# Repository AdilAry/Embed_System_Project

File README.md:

Battery management system for a 4-cell LiFePO4 pack: plug-in board for an STM32 NUCLEO-L152RE with per-cell voltage, current and temperature measurement, MOSFET charge/discharge switching, and Modbus RTU over RS-485. Designed in KiCad, simulated in LTspice, built and tested.

---
### Project specification;
---
#### Battery details:
**4 cell Lithium Iron Phosphate battery.**

Cell voltage: 3.2 V

Cell capacity: 105 Ah

Charge voltage maximum: 3.65 V

Discharge cutoff voltage: 2.5 V

---
Battery full specifications can be found here: https://www.18650batterystore.com/products/eve-lf105

---
#### Requirements;
- Temperature monitoring (via two sensors).
- Individual battery cell voltages measurement.
- MOSFET driven switch (both charging and discharging).
- Current measurement, including over current protection (10A).
- STM32 controller with over/under voltage per cell (2.5V min, 3.65V max. per cell), over/under temperature (charge: 0C to 40C and discharge: -20C to 40C).
- Plugin design to connect a NUCLEO-L152RE board to the BMS circuit.

---
### Platform/software choices;
Version Control - Git, GitHub.

CAD - KiCAD.

Circuit Simulation - LTspice.

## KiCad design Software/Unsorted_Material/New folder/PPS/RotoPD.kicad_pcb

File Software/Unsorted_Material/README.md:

# helloooee

## Getting started

To make it easy for you to get started with GitLab, here's a list of recommended next steps.

Already a pro? Just edit this README.md and make it your own. Want to make it easy? [Use the template at the bottom](#editing-this-readme)!

## Add your files

- [ ] [Create](https://docs.gitlab.com/ee/user/project/repository/web_editor.html#create-a-file) or [upload](https://docs.gitlab.com/ee/user/project/repository/web_editor.html#upload-a-file) files
- [ ] [Add files using the command line](https://docs.gitlab.com/topics/git/add_files/#add-files-to-a-git-repository) or push an existing Git repository with the following command:

```
cd existing_repo
git remote add origin http://gitlab.local/root/hello.git
git branch -M main
git push -uf origin main
```

## Integrate with your tools

- [ ] [Set up project integrations](http://gitlab.local/root/hello/-/settings/integrations)

## Collaborate with your team

- [ ] [Invite team members and collaborators](https://docs.gitlab.com/ee/user/project/members/)
- [ ] [Create a new merge request](https://docs.gitlab.com/ee/user/project/merge_requests/creating_merge_requests.html)
- [ ] [Automatically close issues from merge requests](https://docs.gitlab.com/ee/user/project/issues/managing_issues.html#closing-issues-automatically)
- [ ] [Enable merge request approvals](https://docs.gitlab.com/ee/user/project/merge_requests/approvals/)
- [ ] [Set auto-merge](https://docs.gitlab.com/user/project/merge_requests/auto_merge/)

## Test and Deploy

Use the built-in continuous integration in GitLab.

- [ ] [Get started with GitLab CI/CD](https://docs.gitlab.com/ee/ci/quick_start/)
- [ ] [Analyze your code for known vulnerabilities with Static Application Security Testing (SAST)](https://docs.gitlab.com/ee/user/application_security/sast/)
- [ ] [Deploy to Kubernetes, Amazon EC2, or Amazon ECS using Auto Deploy](https://docs.gitlab.com/ee/topics/autodevops/requirements.html)
- [ ] [Use pull-based deployments for improved Kubernetes management](https://docs.gitlab.com/ee/user/clusters/agent/)
- [ ] [Set up protected environments](https://docs.gitlab.com/ee/ci/environments/protected_environments.html)

***

# Editing this README

When you're ready to make this README your own, just edit this file and use the handy template below (or feel free to structure it however you want - this is just a starting point!). Thanks to [makeareadme.com](https://www.makeareadme.com/) for this template.

## Suggestions for a good README

Every project is different, so consider which of these sections apply to yours. The sections used in the template are suggestions for most open source projects. Also keep in mind that while a README can be too long and detailed, too long is better than too short. If you think your README is too long, consider utilizing another form of documentation rather than cutting out information.

## Name
Choose a self-explaining name for your project.

## Description
Let people know what your project can do specifically. Provide context and add a link to any reference visitors might be unfamiliar with. A list of Features or a Background subsection can also be added here. If there are alternatives to your project, this is a good place to list differentiating factors.

## Badges
On some READMEs, you may see small images that convey metadata, such as whether or not all the tests are passing for the project. You can use Shields to add some to your README. Many services also have instructions for adding a badge.

## Visuals
Depending on what you are making, it can be a good idea to include screenshots or even a video (you'll frequently see GIFs rather than actual videos). Tools like ttygif can help, but check out Asciinema for a more sophisticated method.

## Installation
Within a particular ecosystem, there may be a common way of installing things, such as using Yarn, NuGet, or Homebrew. However, consider the possibility that whoever is reading your README is a novice and would like more guidance. Listing specific steps helps remove ambiguity and gets people to using your project as quickly as possible. If it only runs in a specific context like a particular programming language version or operating system or has dependencies that have to be installed manually, also add a Requirements subsection.

## Usage
Use examples liberally, and show the expected output if you can. It's helpful to have inline the smallest example of usage that you can demonstrate, while providing links to more sophisticated examples if they are too long to reasonably include in the README.

## Support
Tell people where they can go to for help. It can be any combination of an issue tracker, a chat room, an email address, etc.

## Roadmap
If you have ideas for releases in the future, it is a good idea to list them in the README.

## Contributing
State if you are open to contributions and what your requirements are for accepting them.

For people who want to make changes to your project, it's helpful to have some documentation on how to get started. Perhaps there is a script that they should run or some environment variables that they need to set. Make these steps explicit. These instructions could also be useful to your future self.

You can also document commands to lint the code or run tests. These steps help to ensure high code quality and reduce the likelihood that the changes inadvertently break something. Having instructions for running tests is especially helpful if it requires external setup, such as starting a Selenium server for testing in a browser.

## Authors and acknowledgment
Show your appreciation to those who have contributed to the project.

## License
For open source projects, say how it is licensed.

## Project status
If you have run out of energy or time for your project, put a note at the top of the README saying that development has slowed down or stopped completely. Someone may choose to fork your project or volunteer to step in as a maintainer or owner, allowing your project to keep going. You can also make an explicit request for maintainers.

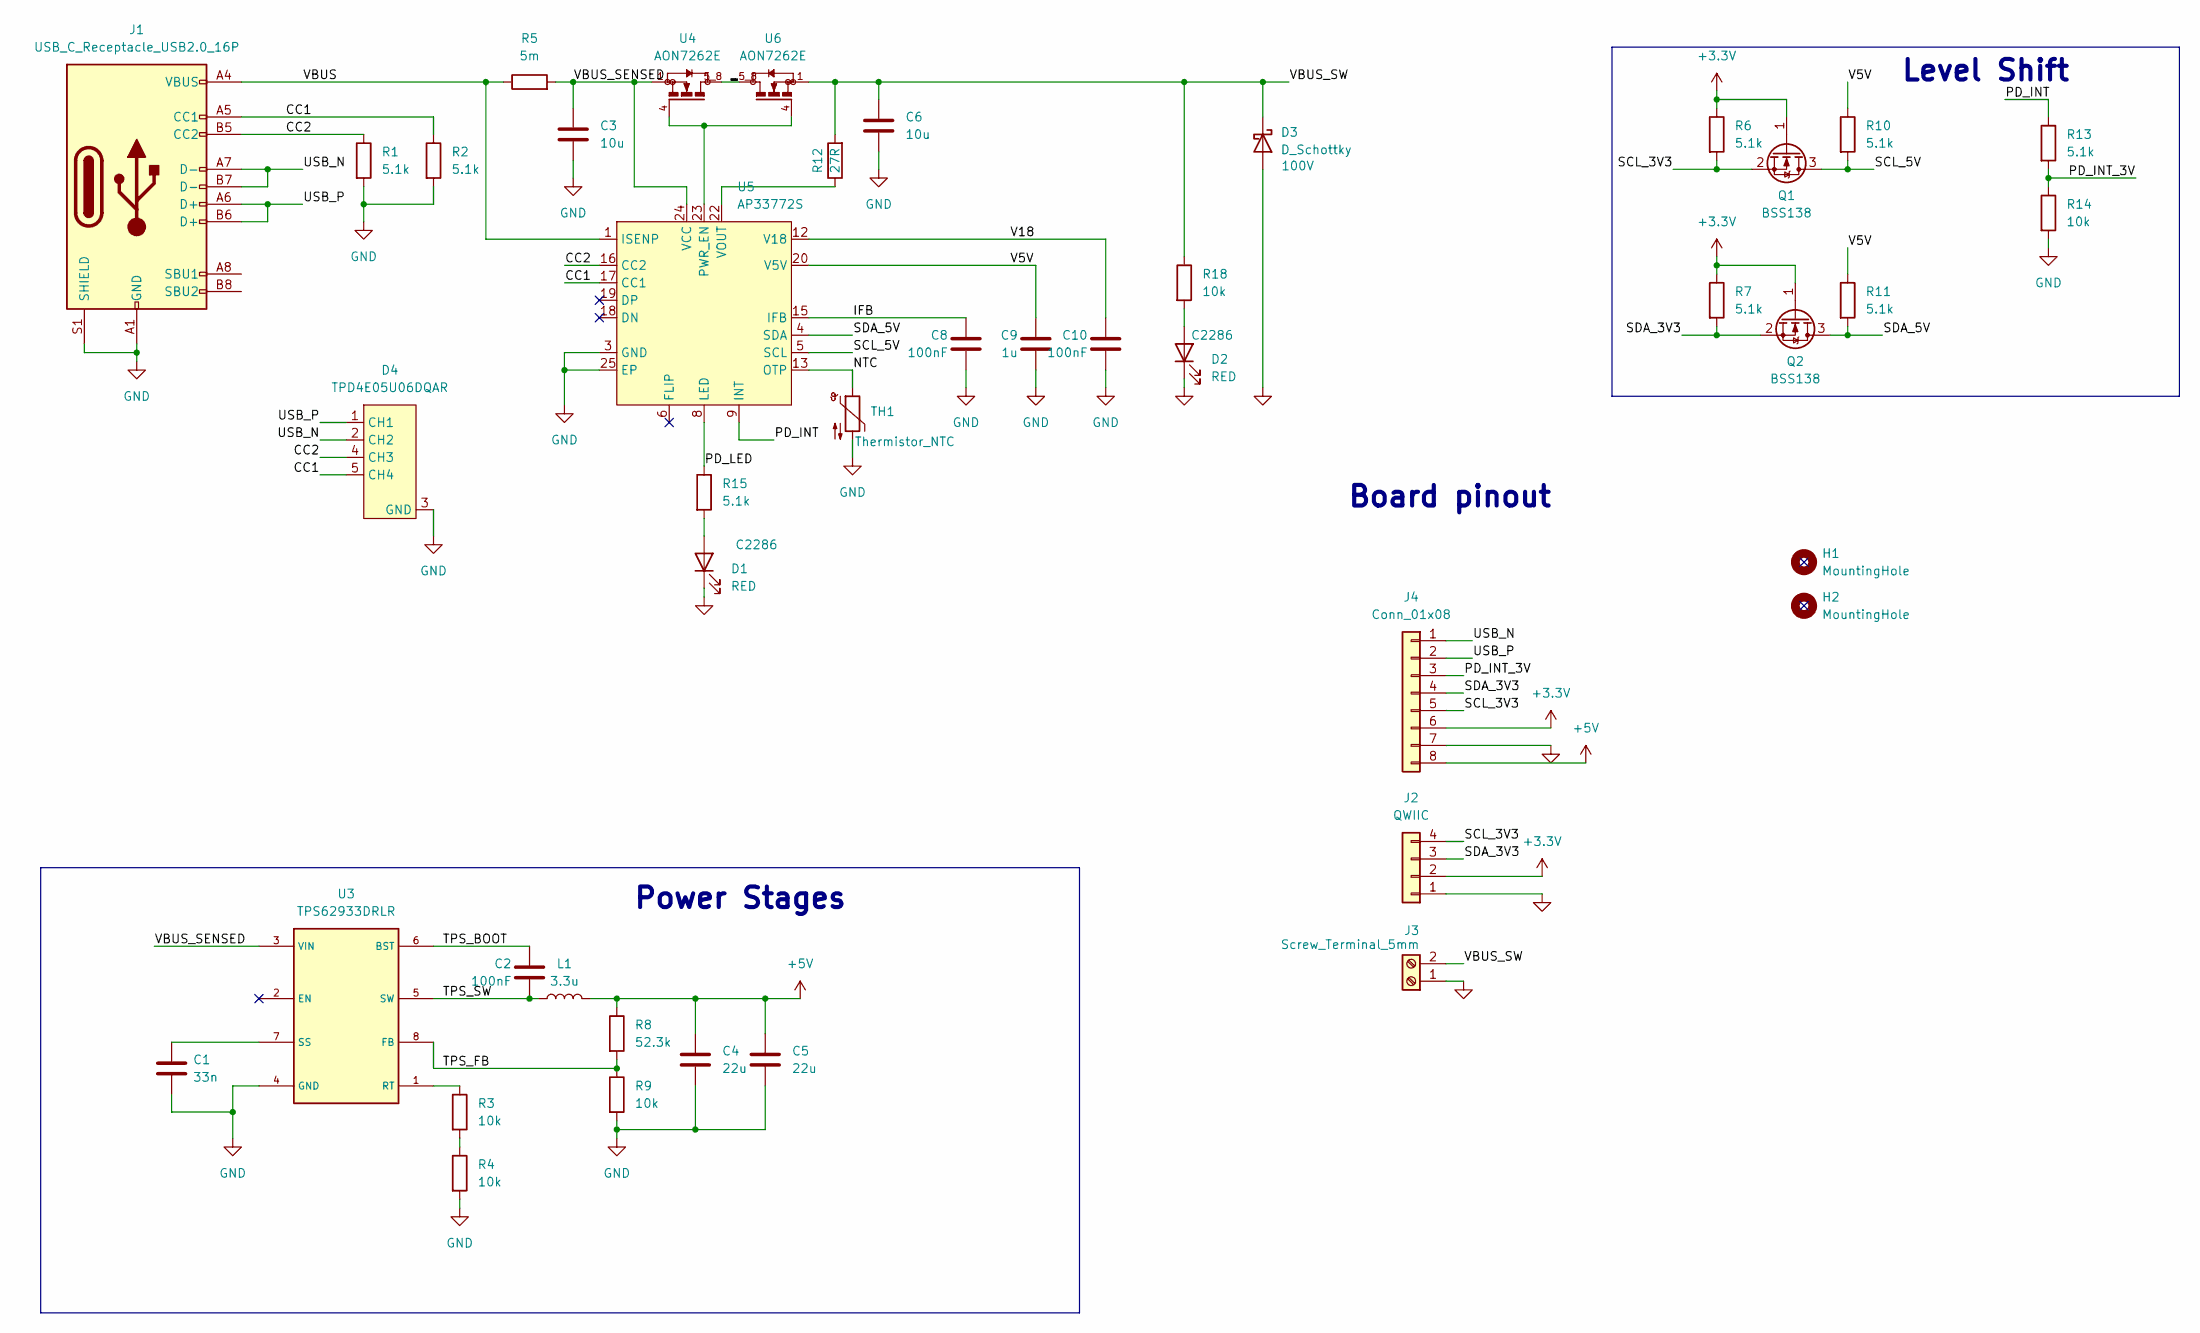
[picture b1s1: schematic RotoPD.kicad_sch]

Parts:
C1: 33n; C_0603_1608Metric; LCSC C21117
C2, C8, C10: 100nF; C_0402_1005Metric; LCSC C1525
C3, C6: 10u; C_1206_3216Metric; LCSC C513774
C4, C5: 22u; C_0805_2012Metric; LCSC C45783
C9: 1u; C_0603_1608Metric; LCSC C15849
D1, D2: RED; LED_0603_1608Metric; LCSC C2286
D3: D_Schottky; D_SMA; Voltage 100V; LCSC C14996
D4: TPD4E05U06DQAR; SON50P100X255X50-10N
H1, H2: MountingHole; MountingHole_2.7mm_M2.5_DIN965_Pad_TopBottom
J1: USB_C_Receptacle_USB2.0_16P; USB_C_GSwitch
J2: QWIIC; JST_SH_SM04B-SRSS-TB_1x04-1MP_P1.00mm_Horizontal; LCSC C160404
J3: Screw_Terminal_5mm; TerminalBlock_Phoenix_MKDS-1,5-2_1x02_P5.00mm_Horizontal
J4: Conn_01x08; PinHeader_1x08_P2.54mm_Vertical
L1: 3.3u; L_Bourns_SRP7028A_7.3x6.6mm
Q1: BSS138; SOT-323_SC-70
Q2: BSS138; SOT-323_SC-70; JLCPCB Rotation Offset 180
R1, R2, R6, R7, R10, R11, R13, R15: 5.1k; R_0402_1005Metric; LCSC C25905
R3, R4, R9, R14, R18: 10k; R_0402_1005Metric; LCSC C25744
R5: 5m; R_0805_2012Metric; Part # PA0805FRE470R005L; LCSC C728267
R8: 52.3k; R_0402_1005Metric; LCSC C103091
R12: 27R; R_0402_1005Metric; LCSC C138021
TH1: Thermistor_NTC; R_0402_1005Metric; LCSC C77131
U3: TPS62933DRLR; SOT583
U4, U6: AON7262E; DFN-8(3.3x3.3)
U5: AP33772S; QFN-24-1EP_4x4mm_P0.5mm_EP2.6x2.6mm; LCSC C9900152998

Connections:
+3.3V: J2.2, J4.6, Q1.1 (G), Q2.1 (G), R6.1, R7.1
+5V: C4.1, C5.1, J4.8, L1.2, R8.1
/CC1: D4.5 (CH4), D4.6, J1.A5 (CC1), R2.1, U5.17 (CC1)
/CC2: D4.4 (CH3), D4.7, J1.B5 (CC2), R1.1, U5.16 (CC2)
/IFB: C8.1, U5.15 (IFB)
/NMOS: U4.5_8, U6.5_8
/NTC: TH1.1, U5.13 (OTP)
/PD_INT: R13.1, U5.9 (INT)
/PD_INT_3V: J4.3, R13.2, R14.1
/PD_LED: R15.1, U5.8 (LED)
/SCL_3V3: J2.4, J4.5, Q1.2 (S), R6.2
/SCL_5V: Q1.3 (D), R10.2, U5.5 (SCL)
/SDA_3V3: J2.3, J4.4, Q2.2 (S), R7.2
/SDA_5V: Q2.3 (D), R11.2, U5.4 (SDA)
/TPS_BOOT: C2.1, U3.6 (BST)
/TPS_FB: R8.2, R9.1, U3.8 (FB)
/TPS_SW: C2.2, L1.1, U3.5 (SW)
/USB_N: D4.2 (CH2), D4.9, J1.A7 (D-), J1.B7 (D-), J4.1
/USB_P: D4.1 (CH1), D4.10, J1.A6 (D+), J1.B6 (D+), J4.2
/V5V: C9.1, R10.1, R11.1, U5.20 (V5V)
/V18: C10.1, U5.12 (V18)
/VBUS: J1.A4 (VBUS), J1.A9 (VBUS), J1.B4 (VBUS), J1.B9 (VBUS), R5.1, U5.1 (ISENP)
/VBUS_SENSED: C3.1, R5.2, U3.3 (VIN), U4.1, U4.2, U4.3, U5.24 (VCC)
/VBUS_SW: C6.1, D3.1 (K), J3.2, R12.2, R18.1, U6.1, U6.2, U6.3
GND: C1.2, C3.2, C4.2, C5.2, C6.2, C8.2, C9.2, C10.2, D1.1 (K), D2.1 (K), D3.2 (A), D4.3 (GND), D4.8 (GND), J1.A1 (GND), J1.A12 (GND), J1.B1 (GND), J1.B12 (GND), J1.S1 (SHIELD), J2.1, J3.1, J4.7, R1.2, R2.2, R4.2, R9.2, R14.2, TH1.2, U3.4 (GND), U5.3 (GND), U5.25 (EP)
unnamed: D1.2 (A), R15.2
unnamed: D2.2 (A), R18.2
unnamed: R3.2, R4.1
unnamed: R3.1, U3.1 (RT)
unnamed: C1.1, U3.7 (SS)
unnamed: U5.2 (NC), U5.7 (NC), U5.10 (NC), U5.11 (NC), U5.14 (NC), U5.21 (NC)
unnamed: U4.4, U5.23 (PWR_EN), U6.4
unnamed: R12.1, U5.22 (VOUT)

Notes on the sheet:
Power Stages
Level Shift
Board pinout

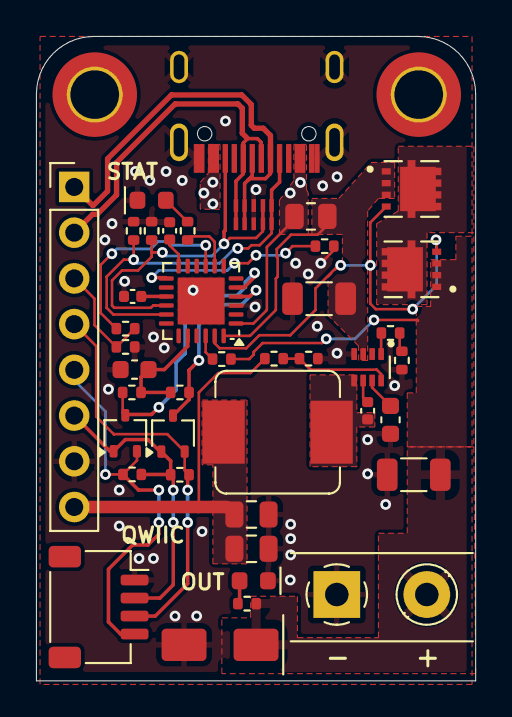
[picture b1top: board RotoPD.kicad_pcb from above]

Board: 2 copper layers, 24.4 x 35.8 mm, 43 parts (0 on the bottom side), 33 nets.

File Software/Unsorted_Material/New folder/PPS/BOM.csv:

"Reference","Value","Footprint","Qty","DNP"
"C1","33n","Capacitor_SMD:C_0603_1608Metric","1",""
"C2,C8,C10","100nF","Capacitor_SMD:C_0402_1005Metric","3",""
"C3,C6","10u","Capacitor_SMD:C_1206_3216Metric","2",""
"C4,C5","22u","Capacitor_SMD:C_0805_2012Metric","2",""
"C9","1u","Capacitor_SMD:C_0603_1608Metric","1",""
"D1,D2","RED","LED_SMD:LED_0603_1608Metric","2",""
"D3","D_Schottky","Diode_SMD:D_SMA","1",""
"D4","TPD4E05U06DQAR","Diode_TVS:SON50P100X255X50-10N","1",""
"J1","USB_C_Receptacle_USB2.0_16P","Connector_USBC:USB_C_GSwitch","1",""
"J2","QWIIC","Connector_JST:JST_SH_SM04B-SRSS-TB_1x04-1MP_P1.00mm_Horizontal","1",""
"J3","Screw_Terminal_5mm","TerminalBlock_Phoenix:TerminalBlock_Phoenix_MKDS-1,5-2_1x02_P5.00mm_Horizontal","1",""
"J4","Conn_01x08","Connector_PinHeader_2.54mm:PinHeader_1x08_P2.54mm_Vertical","1",""
"L1","3.3u","Inductor_SMD:L_Bourns_SRP7028A_7.3x6.6mm","1",""
"Q1,Q2","BSS138","Package_TO_SOT_SMD:SOT-323_SC-70","2",""
"R1,R2,R6,R7,R10,R11,R13,R15","5.1k","Resistor_SMD:R_0402_1005Metric","8",""
"R3,R4,R9,R14,R18","10k","Resistor_SMD:R_0402_1005Metric","5",""
"R5","5m","Resistor_SMD:R_0805_2012Metric","1",""
"R8","52.3k","Resistor_SMD:R_0402_1005Metric","1",""
"R12","27R","Resistor_SMD:R_0402_1005Metric","1",""
"TH1","Thermistor_NTC","Resistor_SMD:R_0402_1005Metric","1",""
"U3","TPS62933DRLR","Power_Converter:SOT583","1",""
"U4,U6","AON7262E","Transistor_MOSFET:DFN-8(3.3x3.3)","2",""
"U5","AP33772S","Interface_USBC:QFN-24-1EP_4x4mm_P0.5mm_EP2.6x2.6mm","1",""

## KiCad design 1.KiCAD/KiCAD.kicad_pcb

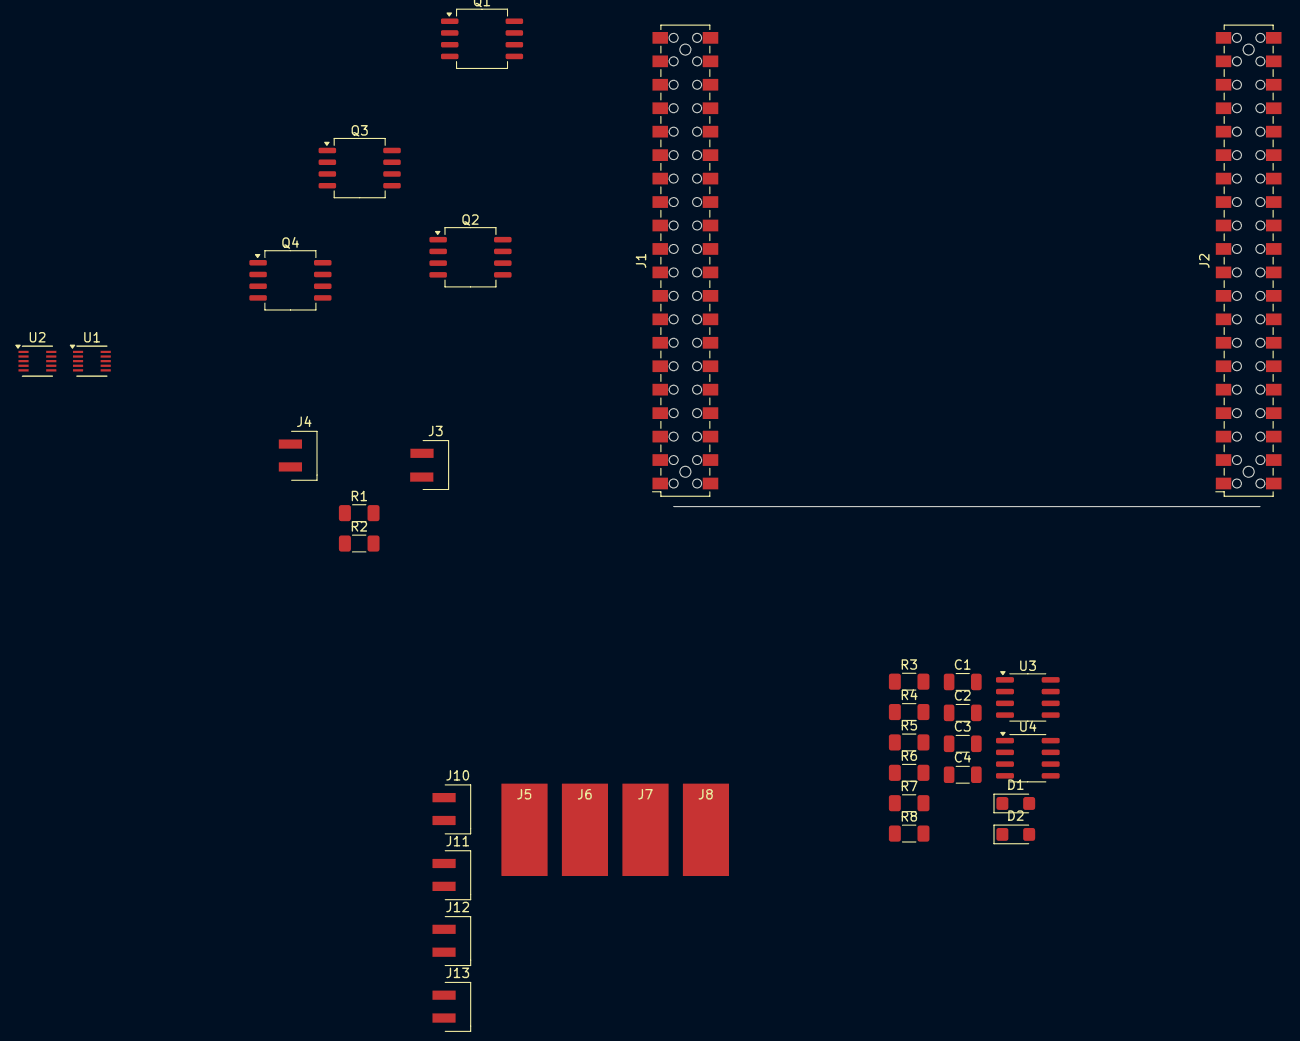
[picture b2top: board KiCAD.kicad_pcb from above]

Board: 2 copper layers, 34 parts (0 on the bottom side), 21 nets, no tracks yet.

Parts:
C1, C2, C3, C4: 100NF_50V_CER; C1206
D1, D2: 3.3V; D_SMF
J1, J2: Conn_02x20_Odd_Even; Samtec_HLE-120-02-xxx-DV-BE-LC_2x20_P2.54mm_Horizontal
J3, J4: TEMP; PinHeader_1x02_P2.54mm_Vertical_SMD_Pin1Left
J5: BAT+; SolderWirePad_1x01_SMD_5x10mm
J6: BAT-; SolderWirePad_1x01_SMD_5x10mm
J7: LOAD+; SolderWirePad_1x01_SMD_5x10mm
J8: LOAD-; SolderWirePad_1x01_SMD_5x10mm
J10: CELL_1; PinHeader_1x02_P2.54mm_Vertical_SMD_Pin1Left
J11: CELL_2; PinHeader_1x02_P2.54mm_Vertical_SMD_Pin1Left
J12: CELL_3; PinHeader_1x02_P2.54mm_Vertical_SMD_Pin1Left
J13: CELL_4; PinHeader_1x02_P2.54mm_Vertical_SMD_Pin1Left
Q1, Q3: Charge; SOIC-8_5.3x6.2mm_P1.27mm
Q2, Q4: Discharge; SOIC-8_5.3x6.2mm_P1.27mm
R1, R2, R3, R4, R7, R8: 10k; 1206
R5: 1m; 1206
R6: 160R; 1206
U1, U2: MUX; TSSOP-10_3x3mm_P0.5mm
U3, U4: AD8021AR; SOIC-8_3.9x4.9mm_P1.27mm

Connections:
3.3V: J1.16, R7.2
+3.3V: J3.1, J4.1
BAT+: C1.1, C4.1, J5.1, J7.1, R3.2, U3.8 (VS+), U4.8 (VS+)
BAT-: C3.2, J6.1, R5.1, U3.1 (-IN)
GND: R1.1, R2.1, R4.1, R8.1, U4.5 (VS-)
LOAD-: C2.2, J8.1, Q1.1 (S), Q3.1 (S)
unnamed: C1.2, C2.1
unnamed: C3.1, C4.2
unnamed: D1.2 (A), U3.7 (Out)
unnamed: D2.2 (A), U4.7 (Out)
unnamed: Q1.8 (D), Q2.8 (D), Q3.8 (D), Q4.8 (D)
unnamed: Q2.1 (S), Q4.1 (S), R5.2, R6.1
unnamed: R6.2, U3.4 (+iN)
unnamed: R7.1, R8.2, U3.6 (REF)
unnamed: R3.1, R4.2, U3.5 (VS-)
PA0: J1.28, Q2.4 (G), Q4.4 (G)
PA1: J1.30, Q1.4 (G), Q3.4 (G)
PA4: D2.1 (K), J1.32
PB0: D1.1 (K), J2.17
PC0: J2.18, J3.2, R1.2
PC1: J2.16, J4.2, R2.2

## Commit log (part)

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2025-09-06 init commit
2025-09-06 Knowledge base added
2025-09-06 setting directory layout
2025-09-06 README little clean up
2025-09-06 example dev commit
2025-09-22 README changes
2025-09-24 README clean up
2025-09-26 Drafts commited, KiCAD libraries moved, Exercise 1 moved
2025-09-27 Minor README changes
2025-09-30 KB clean up
2025-09-30 simul clean up
2025-09-30 obsidian bugged out
2025-09-30 project report course
2025-10-05 Problem 2 added
2025-10-09 Schematic drafts, BOM drafts, Datasheets added
2025-10-09 potential example could be
2025-10-09 BOM finished
2025-10-10 Schematic and PCB V1 done
2025-10-26 misc
2025-10-29 Overhaul_and_Software_section_added
2025-11-10 Report added
2025-11-10 README typo
2025-11-12 pcb pictures added to the presentation
2025-11-12 report
2025-11-12 Course report added
2025-11-14 final version presentation
2025-11-14 presentation finalized
2025-11-15 PCB test report file added
2025-11-16 Communication document
2025-11-18 Manufacturer and soldering documentation
2025-11-19 Add files via upload
    Manufacturer and soldering documentation
2025-12-16 sort out
2025-12-18 Sorted
2025-12-18 forgot about it
